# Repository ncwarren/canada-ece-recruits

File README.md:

# canada-ece-recruits
Repository for the 2017 Paradigm recruitment drive in Canada for PCB submissions

Please email n.warren@mun.ca to be added as a collaborator to the repo

# Submission Guide
1. If unfamiliar with git, learn about what it is. http://rogerdudler.github.io/git-guide/ is a decent usage guide.
2. Clone this repository
3. Create a new directory under the root as your group's name
4. Add, Commit and push your KiCAD files and text file of group member names

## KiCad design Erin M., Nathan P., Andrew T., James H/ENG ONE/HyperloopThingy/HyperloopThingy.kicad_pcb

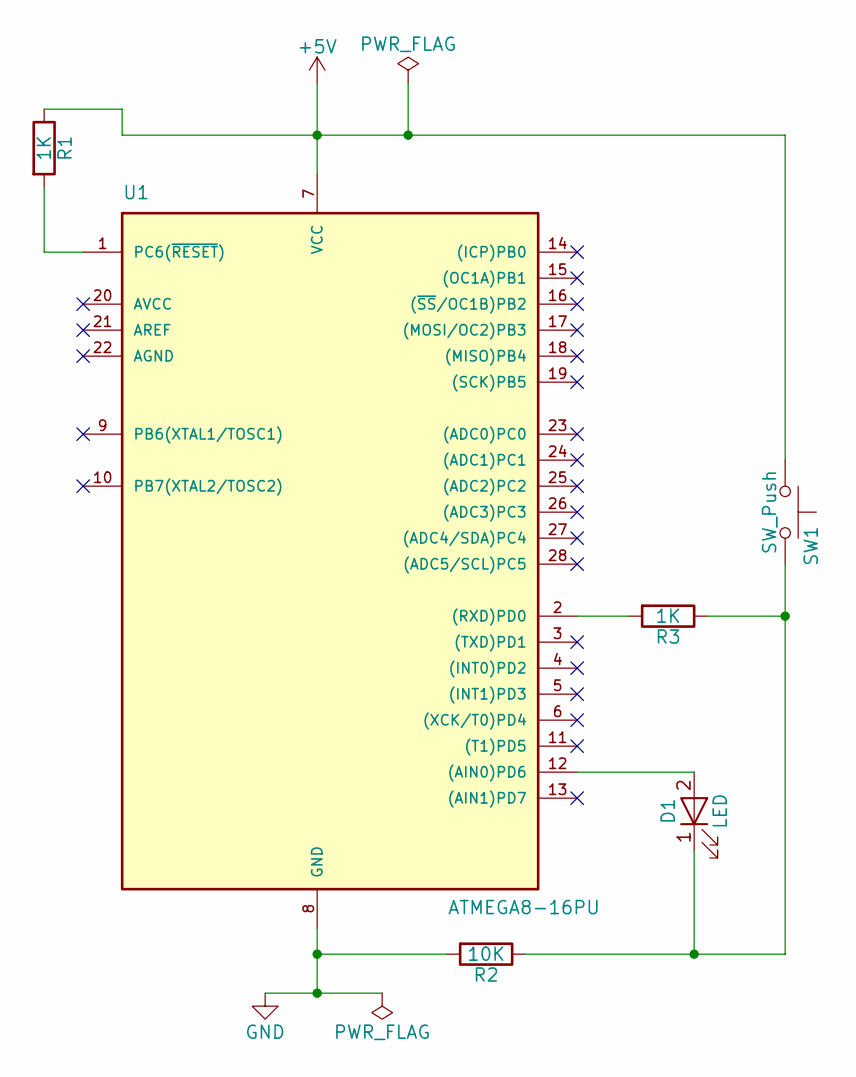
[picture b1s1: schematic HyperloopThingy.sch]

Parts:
D1: LED; LED_1W_3W_R8
R1, R3: 1K; R_0201
R2: 10K; R_0201
SW1: SW_Push; SW_PUSH_6mm
U1: ATMEGA8-16PU; HTSSOP-56-1EP_6.1x14mm_Pitch0.5mm

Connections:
+5V: R1.1, SW1.1, U1.7 (VCC)
GND: R2.2, U1.8 (GND)
unnamed: D1.1 (K), R2.1, R3.1, SW1.2
unnamed: D1.2 (A), U1.12 ((AIN0)PD6)
unnamed: R1.2, U1.1 (PC6(~RESET~))
unnamed: R3.2, U1.2 ((RXD)PD0)

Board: 2 copper layers, 6 parts (0 on the bottom side), 6 nets, no tracks yet.

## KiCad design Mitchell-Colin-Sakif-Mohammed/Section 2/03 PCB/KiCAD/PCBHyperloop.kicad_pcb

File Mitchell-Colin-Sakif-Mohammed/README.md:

### Group Members

Mitchell Stride,
Colin Hunt,
Mohammed Birama,
Sakif Mohammed

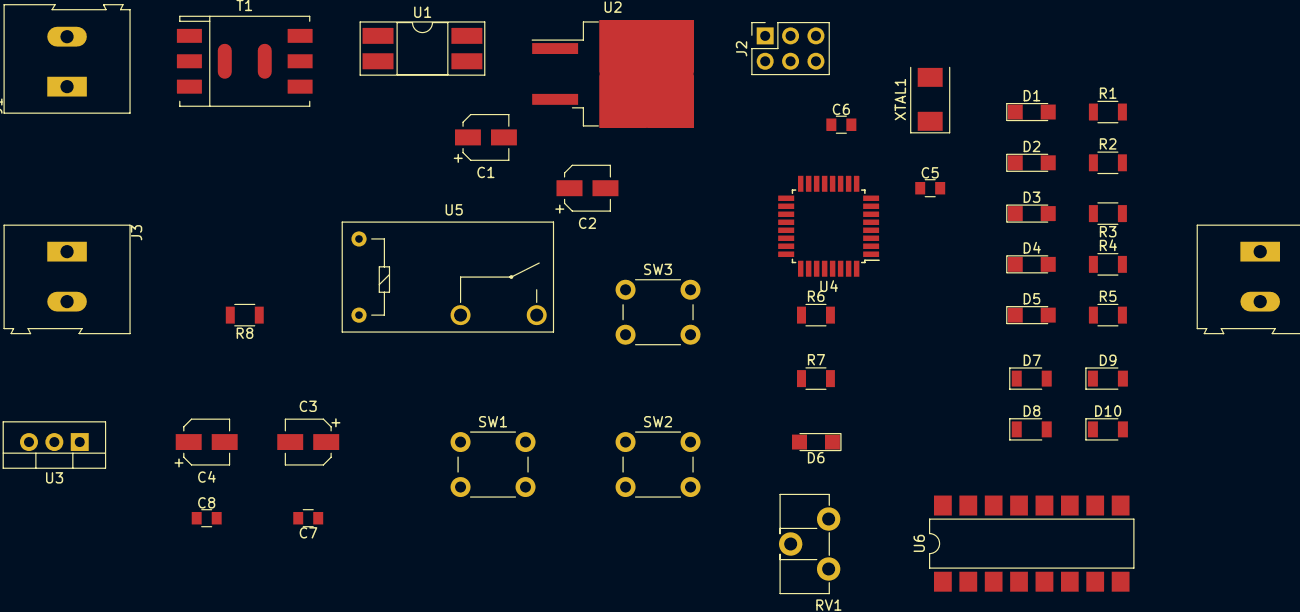
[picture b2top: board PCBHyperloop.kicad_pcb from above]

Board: 2 copper layers, 42 parts (0 on the bottom side), 35 nets, no tracks yet.

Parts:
C1: 600uF; CP_Elec_4x5.3
C2: 47uF; CP_Elec_4x5.3
C3, C4: 10uF; CP_Elec_4x5.3
C5, C6: 22pF; C_0805
C7, C8: 0.1uF; C_0805
D1, D2, D3, D4, D5: LED1; LED_1206
D6: LED6; LED_1206
D7, D8, D9, D10: D; D_1206
J1, J3, J4: Screw_Terminal_01x02; AK300-2
J2: ISP; Socket_Strip_Straight_2x03_Pitch2.54mm
R1, R2, R3, R4, R5, R7, R8: 270; R_1206
R6: 10k; R_1206
RV1: POT; Potentiometer_Trimmer_ACP_CA9h3.8_Vertical_Px3.8mm_Py5.0mm
SW1, SW2, SW3: SW_Push_Dual; SW_PUSH_6mm_h5mm
T1: Transformer_1P_2S; Transformer_NF_ETAL_P2781
U1: IC Temp; DIP-4_W8.89mm_SMDSocket_LongPads
U2: MC78M00; TO-263-2
U3: LM7805_TO220; TO-220_Vertical
U4: ATMEGA328P-AU; TQFP-32_7x7mm_Pitch0.8mm
U5: ASSR-1218; Relay_SPST_OMRON-G5Q
U6: L293NE; SMDIP-16_W7.62mm
XTAL1: 16Mhz; Crystal_SMD_0603-2pin_6.0x3.5mm

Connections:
9Vin: C2.1, U2.3
+5V: C4.1, C7.1, C8.1, J2.2, R6.1, R7.1, RV1.3, U3.3, U4.4, U4.6, U4.18, U4.20, U6.16
+9V: C3.1, U3.1, U5.3
/GPIO: J3.2, R8.2
A0(pin23): R1.2, U4.23
A1(pin24): R2.2, U4.24
A2(pin25): R3.2, U4.25
A3(pin26): R4.2, U4.26
A4(pin27): R5.2, U4.27
A5(pin28): RV1.2, U4.28
GND: C1.2, C2.2, C3.2, C4.2, C5.2, C6.2, C7.2, C8.2, D1.1, D2.1, D3.1, D4.1, D5.1, D6.1, D7.2, D8.2, J2.6, J3.1, RV1.1, U1.2, U2.2, U3.2, U4.3, U4.5, U4.21, U5.2, U6.13
MISO: J2.1, U4.16
MOSI: J2.4, U4.15
MotorEN: U4.12, U6.1
unnamed: C1.1, U1.1, U2.1
unnamed: C5.1, U4.9, XTAL1.1
unnamed: C6.1, U4.10, XTAL1.2
unnamed: D1.2, R1.1
unnamed: D2.2, R2.1
unnamed: D3.2, R3.1
unnamed: D4.2, R4.1
unnamed: D5.2, R5.1
unnamed: D6.2, R7.2
unnamed: D7.1, D9.2, J4.1, U6.3
unnamed: D10.1, U6.8
unnamed: D8.1, D10.2, J4.2, U6.6
unnamed: J1.1, T1.2
unnamed: J1.2, T1.1
unnamed: R8.1, U5.1
unnamed: T1.3, T1.5, U1.3
unnamed: T1.4, T1.6, U1.4
PIN0: SW2.1, U4.30
PIN1: SW1.1, U4.31
RESET: J2.5, R6.2, SW3.1, U4.29
SCK: J2.3, U4.17

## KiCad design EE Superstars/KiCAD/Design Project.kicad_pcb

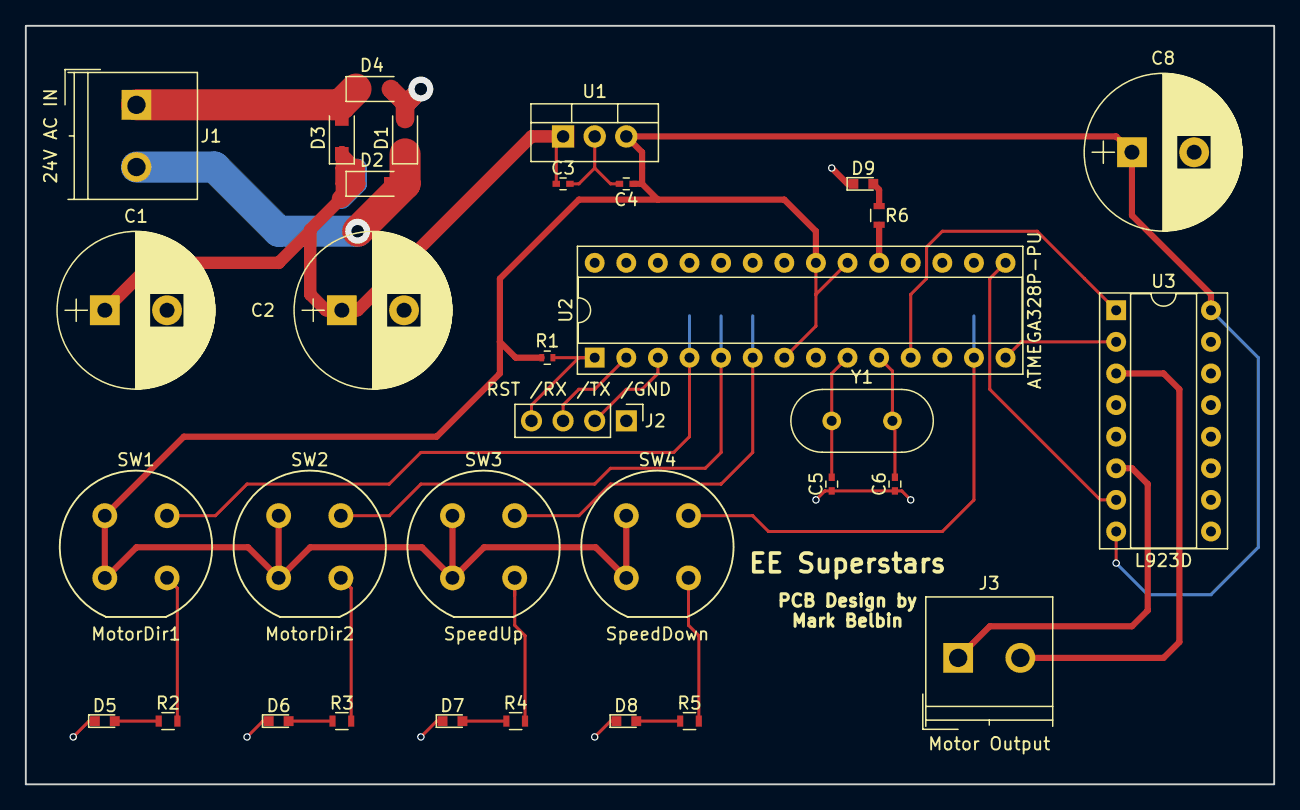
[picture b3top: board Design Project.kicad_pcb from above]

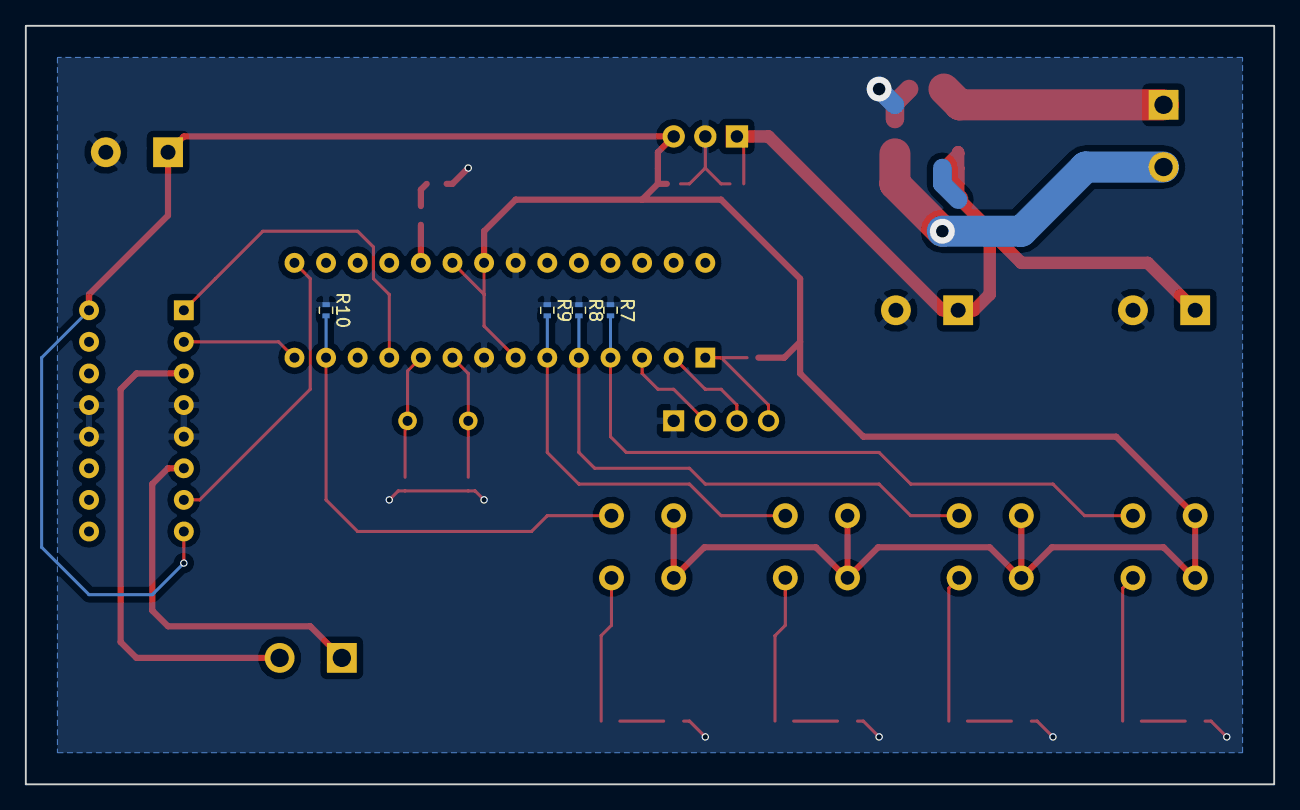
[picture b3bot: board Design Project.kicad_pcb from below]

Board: 2 copper layers, 100.3 x 61.0 mm, 37 parts (4 on the bottom side), 29 nets.

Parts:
C1, C2, C8: 470uF; CP_Radial_D12.5mm_P5.00mm
C3, C4: 0.1uF; C_0402
C5, C6: 22pF; C_0402
D1: D1; D_SOD-123F
D2: D2; D_SOD-123F
D3: D3; D_SOD-123F
D4: DA22F2100L; D_SOD-123F
D5: LED1; LED_0603
D6: LED2; LED_0603
D7: LED3; LED_0603
D8: LED4; LED_0603
D9: LED5; LED_0603
J1: 24V AC IN; TerminalBlock_Philmore_TB132_02x5mm_Straight
J2: RST /RX /TX /GND; Pin_Header_Straight_1x04_Pitch2.54mm
J3: Motor Output; TerminalBlock_Philmore_TB132_02x5mm_Straight
R1, R7, R8, R9, R10: 10K; R_0402
R2, R3, R4, R5, R6: 400R; R_0603
SW1: MotorDir1; Push_E-Switch_KS01Q01
SW2: MotorDir2; Push_E-Switch_KS01Q01
SW3: SpeedUp; Push_E-Switch_KS01Q01
SW4: SpeedDown; Push_E-Switch_KS01Q01
U1: LM7805; TO-220_Vertical
U2: ATMEGA328P-PU; DIP-28_W7.62mm_Socket
U3: L923D; DIP-16_W7.62mm_Socket
Y1: 16 MHz; Crystal_HC49-4H_Vertical

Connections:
5V: C4.1, C8.1, R1.1, SW1.1, SW1.3, SW2.1, SW2.3, SW3.1, SW3.3, SW4.1, SW4.3, U1.3, U2.7, U2.20, U2.21, U3.8, U3.16
DIGPIN2: R7.2, SW1.2, U2.4
DIGPIN3: R8.2, SW2.2, U2.5
DIGPIN4: R9.2, SW3.2, U2.6
DIGPIN5: U2.11, U3.1
DIGPIN7: R10.2, SW4.2, U2.13
DIGPIN8: U2.14, U3.2
DIGPIN9: U2.15, U3.7
GND: C1.2, C2.2, C3.2, C4.2, C5.1, C6.1, C8.2, D1.2, D4.2, D5.1, D6.1, D7.1, D8.1, D9.1, J2.1, R7.1, R8.1, R9.1, R10.1, U1.2, U2.8, U2.22, U3.4, U3.5, U3.12, U3.13
LED5: R6.2, U2.19
unnamed: C1.1, C2.1, C3.1, D2.1, D3.1, U1.1
unnamed: C5.2, U2.9, Y1.1
unnamed: C6.2, U2.10, Y1.2
unnamed: D1.1, D2.2, J1.2
unnamed: D3.2, D4.1, J1.1
unnamed: D5.2, R2.1
unnamed: D6.2, R3.1
unnamed: D7.2, R4.1
unnamed: D8.2, R5.1
unnamed: D9.2, R6.1
unnamed: J2.2, U2.3
unnamed: J2.3, U2.2
unnamed: J2.4, R1.2, U2.1
unnamed: J3.1, U3.6
unnamed: J3.2, U3.3
unnamed: R2.2, SW1.4
unnamed: R3.2, SW2.4
unnamed: R4.2, SW3.4
unnamed: R5.2, SW4.4

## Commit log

2017-10-04 ECE Superstars PCB Deliverable
    Uploaded the PCB KiCAD files, datasheets for components, and a custom BOM!
2017-10-04 Folder Rename
    Properly named our folder "EE Superstars" and not "ECE Superstars".
2017-10-04 intial submission but unfinshed
2017-10-04 Final Submission
    Added sample Arduino-style code for the Atmega328 microcontroller!
2017-10-04 Submitting files
2017-10-04 Battery Model
    Bit of SolidWorks fun
2017-10-05 Added PCB and other docs.
2017-10-05 Upload
    Upload of project files for Nathan Power, James Horner, Andrew Troake, and Erin Maher
2017-10-05 Added BOM
2017-10-05 Upload
    Edited Text File
2017-10-05 changed readme
2017-10-05 mohamed and liam changes
2017-10-05 mohamed and liam changes v2 - error fix
2017-10-06 added final presentation
